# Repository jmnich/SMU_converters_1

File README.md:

# SMU_converters_1

ADC/DAC converters module for HTBlog Source Measure Unit

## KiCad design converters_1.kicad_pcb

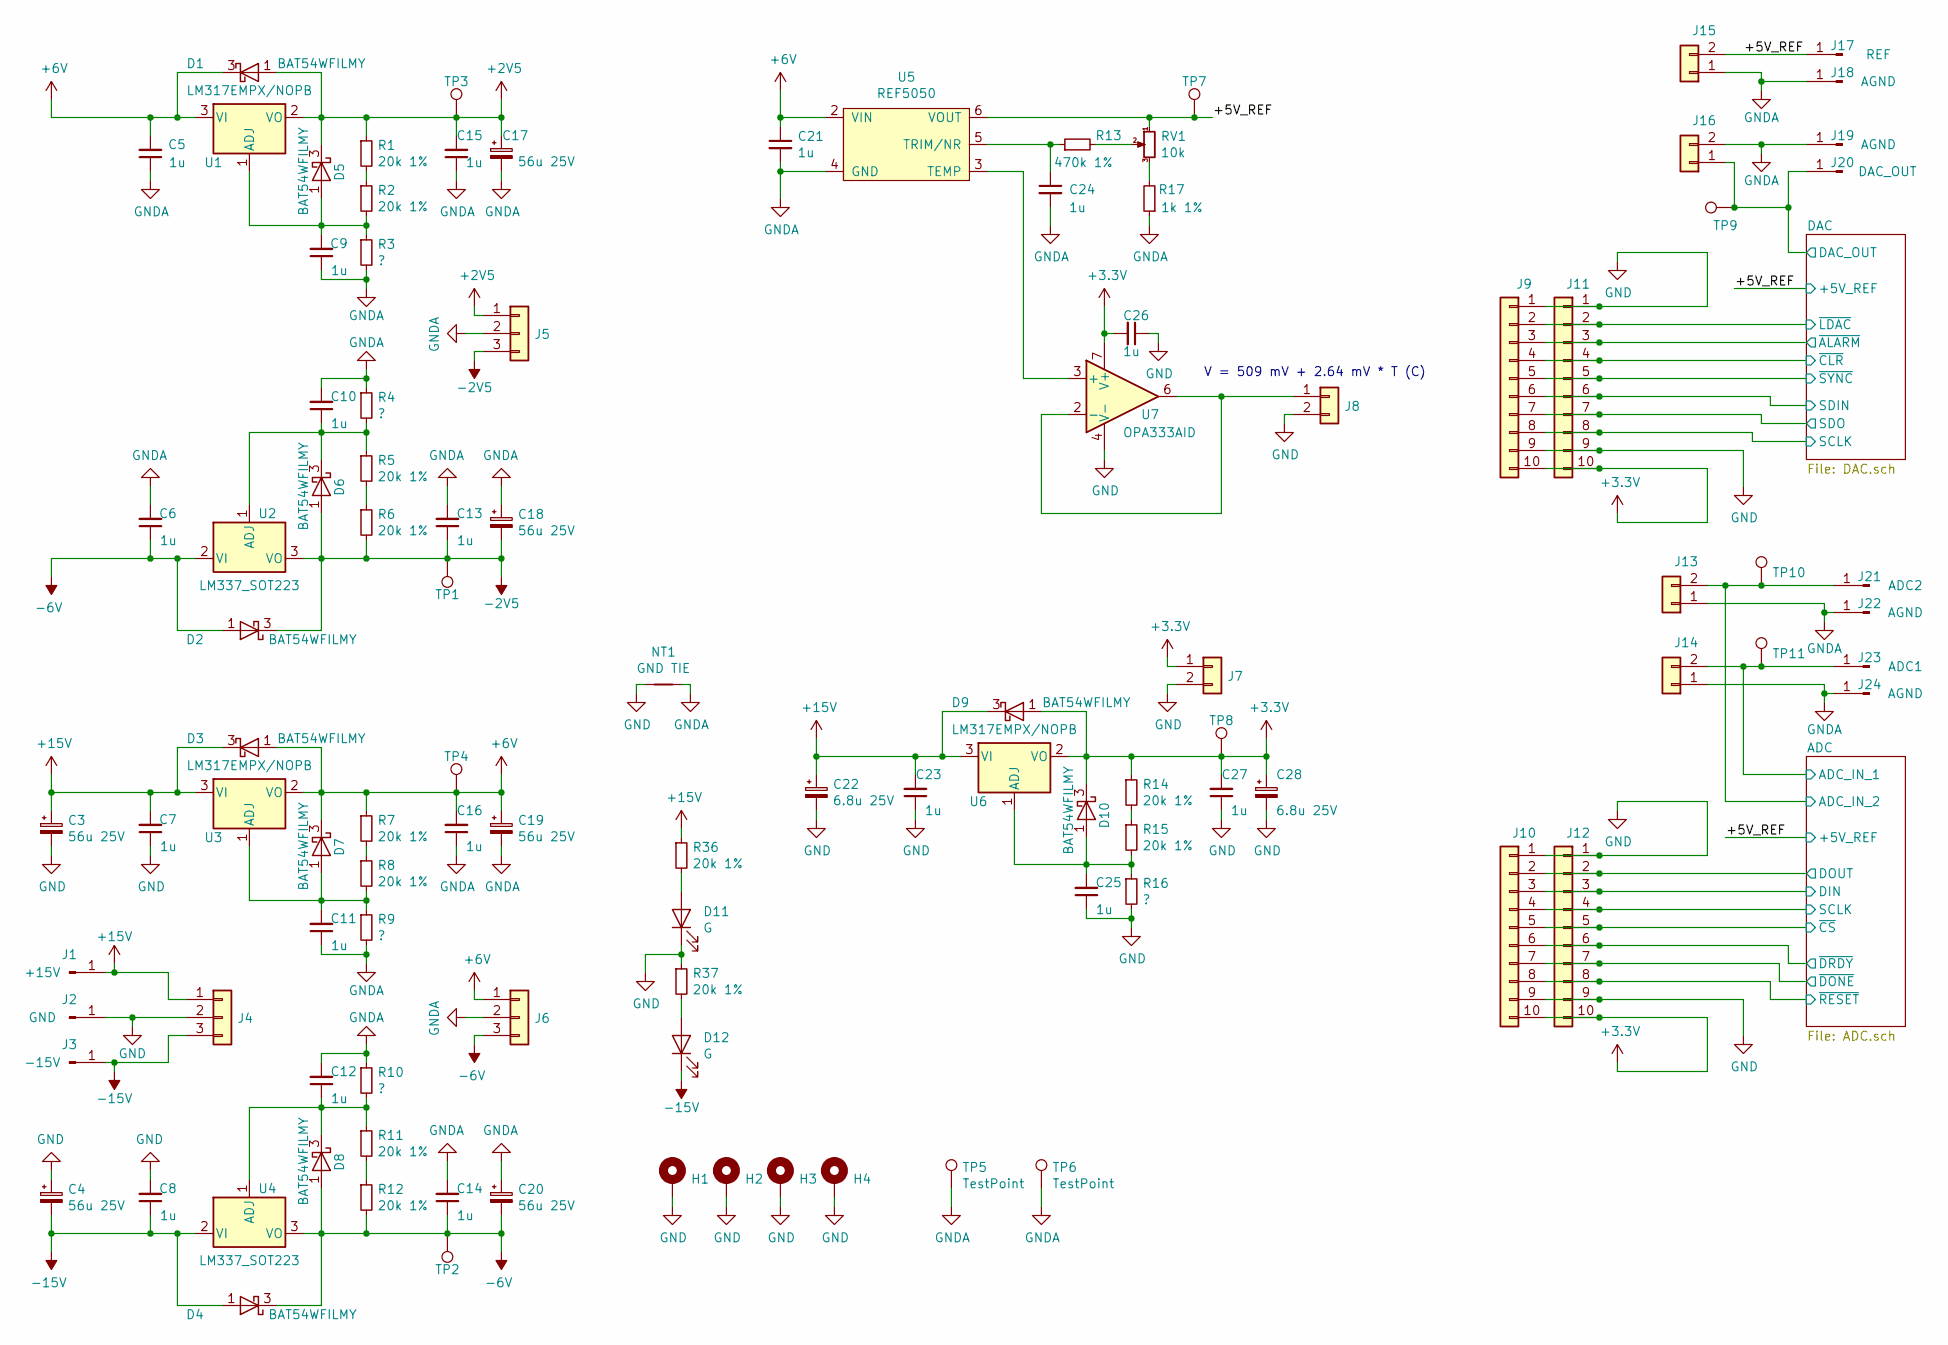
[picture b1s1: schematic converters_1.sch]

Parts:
C3, C4, C17, C18, C19, C20: 56u 25V; CP_Elec_6.3x5.9
C5, C6, C7, C8, C9, C10, C11, C12, C13, C14, C15, C16, C21, C23, C24, C25, C26, C27: 1u; C_0603_1608Metric_Pad1.05x0.95mm_HandSolder
C22, C28: 6.8u 25V; CP_Elec_6.3x5.9
D1, D2, D3, D4, D5, D6, D7, D8, D9, D10: BAT54WFILMY; SOT-323_SC-70
D11, D12: G; LED_0603_1608Metric_Pad1.05x0.95mm_HandSolder
H1, H2, H3, H4: MountingHole_Pad; MountingHole_3.2mm_M3_Pad_Via
J1: +15V; MountingHole_2.2mm_M2_Pad_Via
J2: GND; MountingHole_2.2mm_M2_Pad_Via
J3: -15V; MountingHole_2.2mm_M2_Pad_Via
J4, J5, J6: Conn_01x03; PinHeader_1x03_P2.54mm_Vertical
J7, J8, J13, J14, J15, J16: Conn_01x02; PinHeader_1x02_P2.54mm_Vertical
J9, J10, J11, J12: Conn_01x10; PinHeader_1x10_P2.54mm_Vertical
J17: REF; MountingHole_2.2mm_M2_Pad_Via
J18, J19, J22, J24: AGND; MountingHole_2.2mm_M2_Pad_Via
J20: DAC_OUT; MountingHole_2.2mm_M2_Pad_Via
J21: ADC2; MountingHole_2.2mm_M2_Pad_Via
J23: ADC1; MountingHole_2.2mm_M2_Pad_Via
NT1: GND TIE; NetTie-2_SMD_Pad2.0mm
R1, R2, R5, R6, R7, R8, R11, R12, R14, R15, R36, R37: 20k 1%; R_0603_1608Metric_Pad1.05x0.95mm_HandSolder
R3, R4, R9, R10, R16: ?; R_0603_1608Metric_Pad1.05x0.95mm_HandSolder
R13: 470k 1%; R_0603_1608Metric_Pad1.05x0.95mm_HandSolder
R17: 1k 1%; R_0603_1608Metric_Pad1.05x0.95mm_HandSolder
RV1: 10k; Potentiometer_Vishay_T73XW_Horizontal; MPN T73XW103KT20
TP1, TP2, TP3, TP4, TP5, TP6, TP7, TP8, TP9, TP10, TP11: TestPoint; TestPoint_Keystone_5010-5014_Multipurpose
U1, U3, U6: LM317EMPX/NOPB; SOT-223-3_TabPin2
U2, U4: LM337_SOT223; SOT-223-3_TabPin2
U5: REF5050; SOIC-8_3.9x4.9mm_P1.27mm
U7: OPA333AID; SOIC-8_3.9x4.9mm_P1.27mm

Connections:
+2V5: C15.2, C17.1, D1.1 (A), D5.3 (K), J5.1, R1.1, TP3.1, U1.2 (VO); also elsewhere on the board
+3V3: C26.2, C27.2, C28.1, D9.1 (A), D10.3 (K), J7.1, J9.10, J10.10, J11.10, J12.10, R14.1, TP8.1, U6.2 (VO), U7.7 (V+); also elsewhere on the board
+6V: C5.2, C16.2, C19.1, C21.1, D1.3 (K), D3.1 (A), D7.3 (K), J6.1, R7.1, TP4.1, U1.3 (VI), U3.2 (VO), U5.2 (VIN); also elsewhere on the board
+15V: C3.1, C7.2, C22.1, C23.2, D3.3 (K), D9.3 (K), J1.1, J4.1, R36.1, U3.3 (VI), U6.3 (VI)
-2V5: C13.1, C18.2, D2.3 (K), D6.1 (A), J5.3, R6.2, TP1.1, U2.3 (VO); also elsewhere on the board
-6V: C6.1, C14.1, C20.2, D2.1 (A), D4.3 (K), D8.1 (A), J6.3, R12.2, TP2.1, U2.2 (VI), U4.3 (VO); also elsewhere on the board
-15V: C4.2, C8.1, D4.1 (A), D12.1 (K), J3.1, J4.3, U4.2 (VI)
/+5V_REF: J15.2, J17.1, RV1.1, TP7.1, U5.6 (VOUT); also elsewhere on the board
/ADC/ADC_IN_1: J14.2, J23.1, TP11.1; also elsewhere on the board
/ADC/ADC_IN_2: J13.2, J21.1, TP10.1; also elsewhere on the board
/ADC/DIN: J10.3, J12.3; also elsewhere on the board
/ADC/DOUT: J10.2, J12.2; also elsewhere on the board
/ADC/SCLK: J10.4, J12.4; also elsewhere on the board
/ADC/~CS: J10.5, J12.5; also elsewhere on the board
/ADC/~DONE: J10.7, J12.7; also elsewhere on the board
/ADC/~DRDY: J10.6, J12.6; also elsewhere on the board
/ADC/~RESET: J10.8, J12.8; also elsewhere on the board
/DAC/DAC_OUT: J16.1, J20.1, TP9.1; also elsewhere on the board
/DAC/SCLK: J9.8, J11.8; also elsewhere on the board
/DAC/SDIN: J9.6, J11.6; also elsewhere on the board
/DAC/SDO: J9.7, J11.7; also elsewhere on the board
/DAC/~ALARM: J9.3, J11.3; also elsewhere on the board
/DAC/~CLR: J9.4, J11.4; also elsewhere on the board
/DAC/~LDAC: J9.2, J11.2; also elsewhere on the board
/DAC/~SYNC: J9.5, J11.5; also elsewhere on the board
unnamed: C9.2, D5.1 (A), R2.2, R3.1, U1.1 (ADJ)
unnamed: C10.1, D6.3 (K), R4.2, R5.1, U2.1 (ADJ)
unnamed: C11.2, D7.1 (A), R8.2, R9.1, U3.1 (ADJ)
unnamed: C12.1, D8.3 (K), R10.2, R11.1, U4.1 (ADJ)
unnamed: C24.1, R13.1, U5.5 (TRIM/NR)
unnamed: C25.2, D10.1 (A), R15.2, R16.1, U6.1 (ADJ)
unnamed: D11.2 (A), R36.2
unnamed: D12.2 (A), R37.2
unnamed: J8.1, U7.2 (-), U7.6
unnamed: R1.2, R2.1
unnamed: R5.2, R6.1
unnamed: R7.2, R8.1
unnamed: R11.2, R12.1
unnamed: R13.2, RV1.2
unnamed: R14.2, R15.1
unnamed: R17.2, RV1.3
unnamed: U5.3 (TEMP), U7.3 (+)

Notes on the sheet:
V = 509 mV + 2.64 mV * T (C)

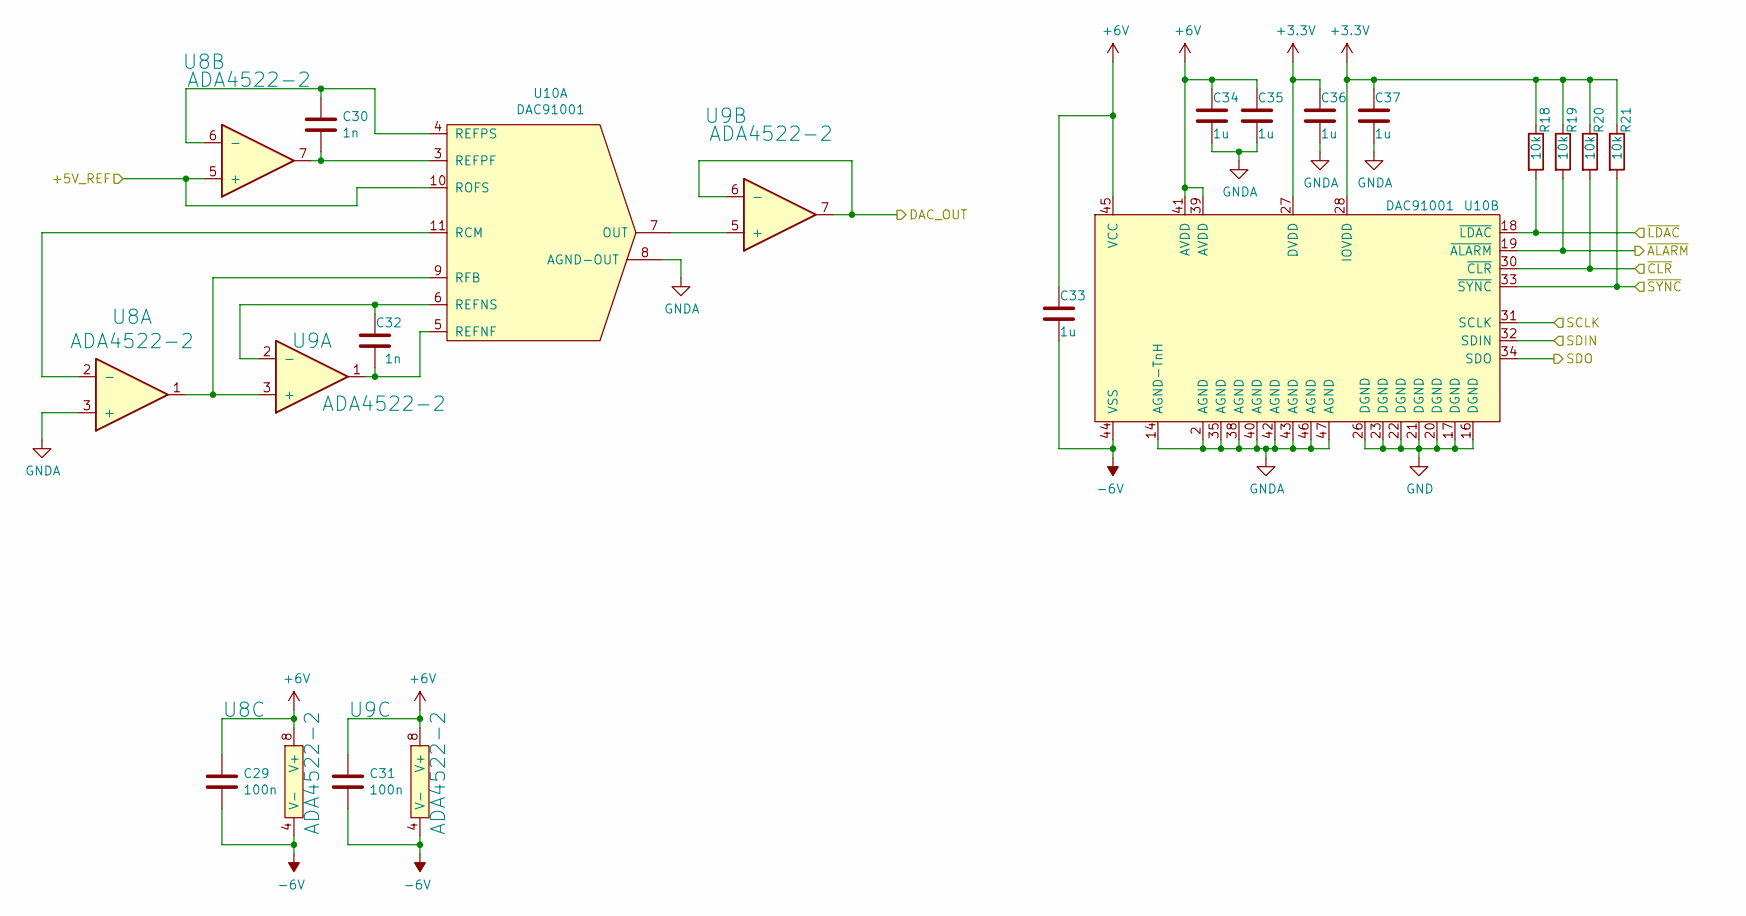
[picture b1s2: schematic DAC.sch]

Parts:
C29, C31: 100n; C_0603_1608Metric_Pad1.05x0.95mm_HandSolder
C30, C32: 1n; C_0603_1608Metric_Pad1.05x0.95mm_HandSolder
C33, C34, C35, C36, C37: 1u; C_0603_1608Metric_Pad1.05x0.95mm_HandSolder
R18, R19, R20, R21: 10k; R_0603_1608Metric_Pad1.05x0.95mm_HandSolder
U8, U9: ADA4522-2; MSOP-8_3x3mm_P0.65mm
U10: DAC91001; TQFP-48_7x7mm_P0.5mm

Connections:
+3V3: C36.1, C37.1, R18.1, R19.1, R20.1, R21.1, U10.27 (DVDD), U10.28 (IOVDD); also elsewhere on the board
+6V: C29.1, C31.1, C33.1, C34.1, C35.1, U8.8 (V+), U9.8 (V+), U10.39 (AVDD), U10.41 (AVDD), U10.45 (VCC); also elsewhere on the board
-6V: C29.2, C31.2, C33.2, U8.4 (V-), U9.4 (V-), U10.44 (VSS); also elsewhere on the board
/+5V_REF: U8.5 (+), U10.10 (ROFS); also elsewhere on the board
/DAC/DAC_OUT: U9.6 (-), U9.7; also elsewhere on the board
/DAC/SCLK: U10.31 (SCLK); also elsewhere on the board
/DAC/SDIN: U10.32 (SDIN); also elsewhere on the board
/DAC/SDO: U10.34 (SDO); also elsewhere on the board
/DAC/~ALARM: R19.2, U10.19 (~ALARM); also elsewhere on the board
/DAC/~CLR: R20.2, U10.30 (~CLR); also elsewhere on the board
/DAC/~LDAC: R18.2, U10.18 (~LDAC); also elsewhere on the board
/DAC/~SYNC: R21.2, U10.33 (~SYNC); also elsewhere on the board
unnamed: C30.1, U8.6 (-), U10.4 (REFPS)
unnamed: C30.2, U8.7, U10.3 (REFPF)
unnamed: C32.1, U9.2 (-), U10.6 (REFNS)
unnamed: C32.2, U9.1, U10.5 (REFNF)
unnamed: U9.5 (+), U10.7 (OUT)
unnamed: U8.1, U9.3 (+), U10.9 (RFB)
unnamed: U8.2 (-), U10.11 (RCM)

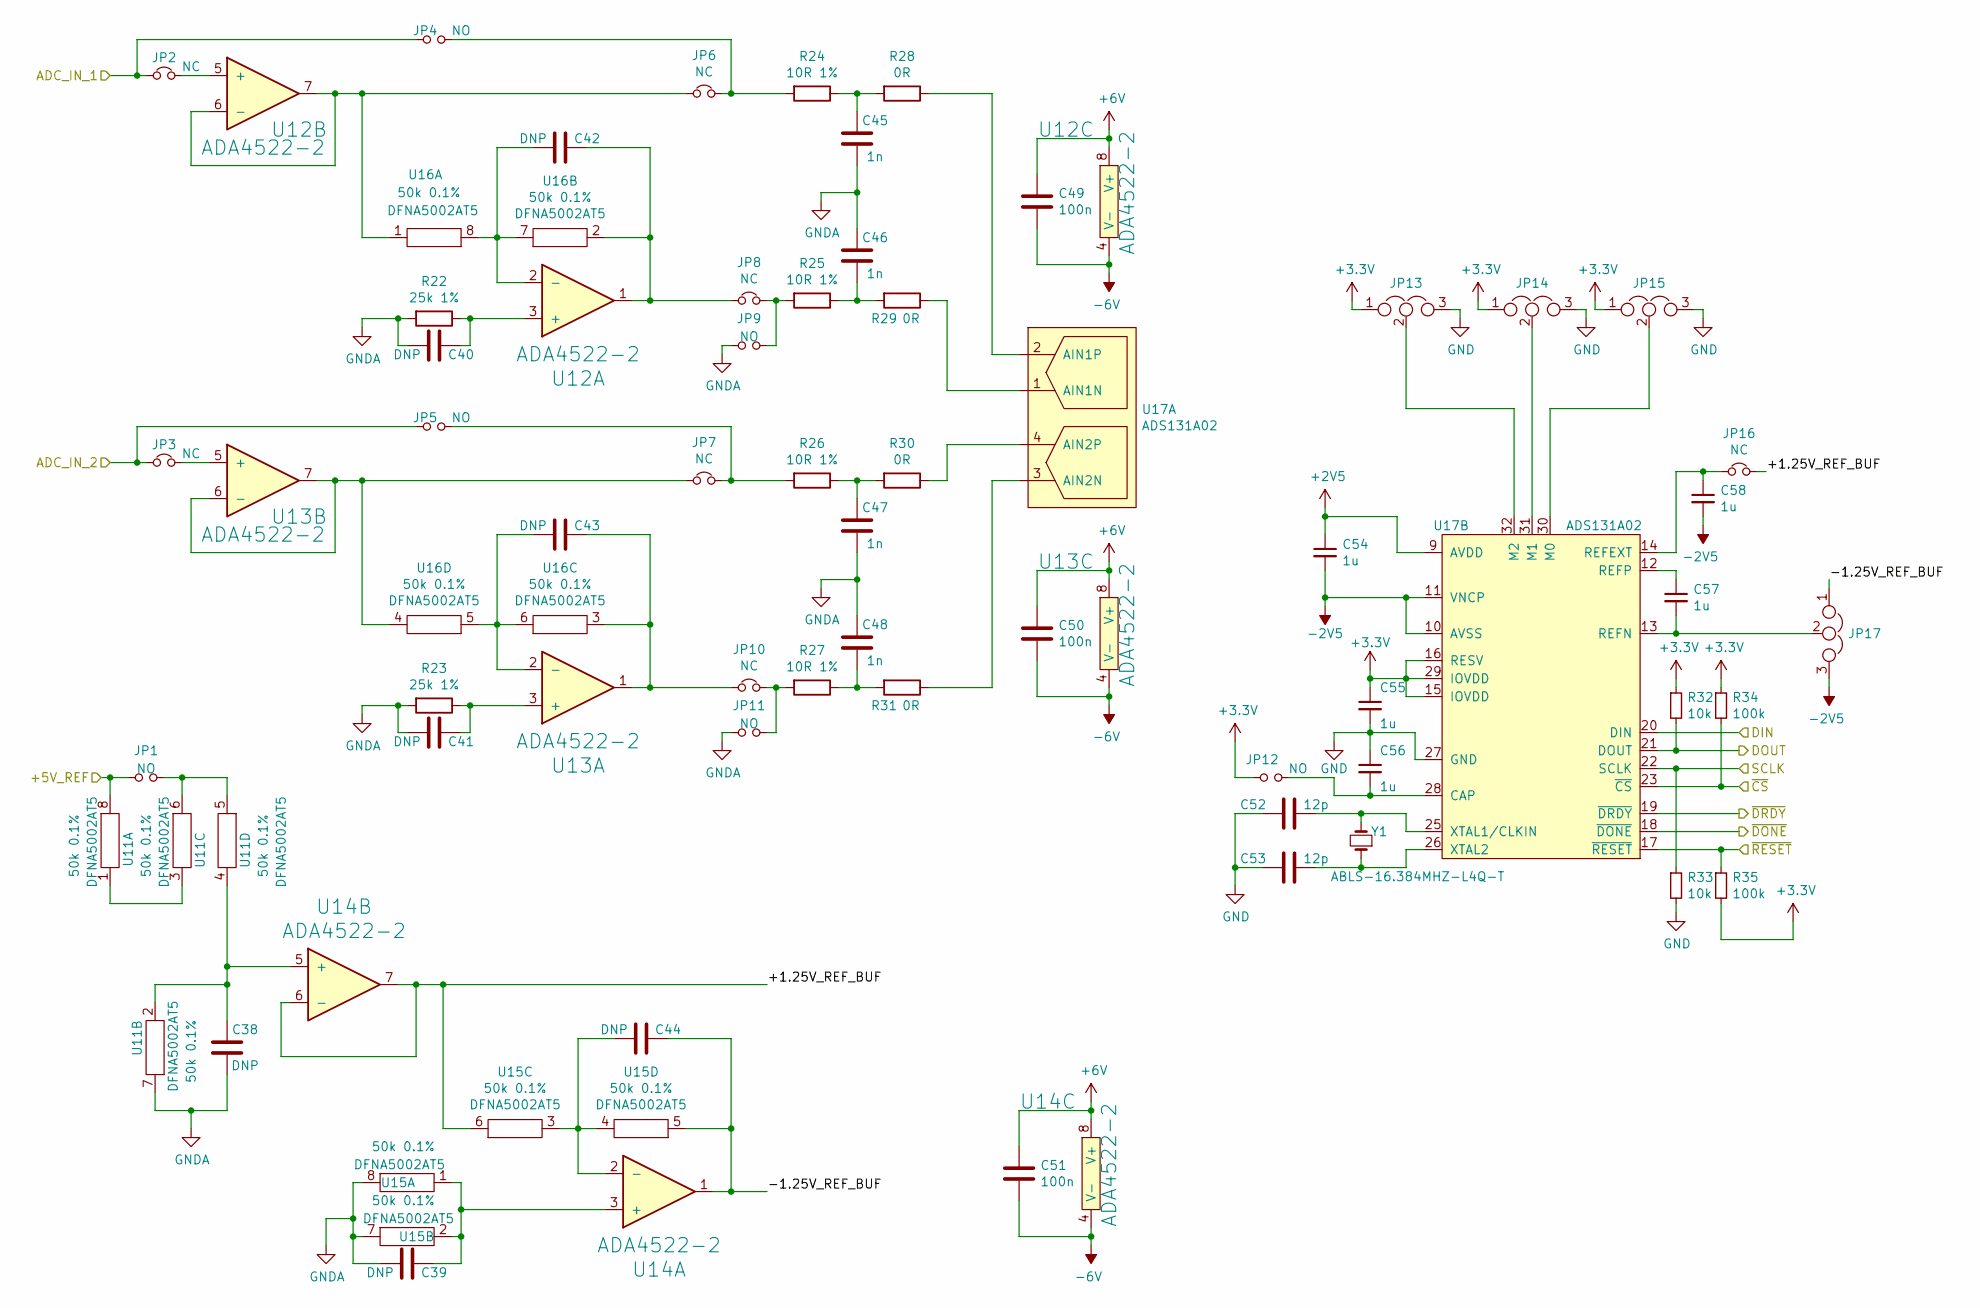
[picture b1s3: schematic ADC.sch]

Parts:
C38, C39, C40, C41, C42, C43, C44: DNP; C_0603_1608Metric_Pad1.05x0.95mm_HandSolder
C45, C46, C47, C48: 1n; C_0603_1608Metric_Pad1.05x0.95mm_HandSolder
C49, C50, C51: 100n; C_0603_1608Metric_Pad1.05x0.95mm_HandSolder
C52, C53: 12p; C_0603_1608Metric_Pad1.05x0.95mm_HandSolder
C54, C55, C56, C57, C58: 1u; C_0603_1608Metric_Pad1.05x0.95mm_HandSolder
JP1, JP4, JP5, JP9, JP11, JP12: NO; SolderJumper-2_P1.3mm_Open_RoundedPad1.0x1.5mm
JP2, JP3, JP6, JP7, JP8, JP10, JP16: NC; SolderJumper-2_P1.3mm_Open_RoundedPad1.0x1.5mm
JP13, JP14, JP15, JP17: Jumper_NC_Dual; SolderJumper-3_P1.3mm_Open_RoundedPad1.0x1.5mm
R22, R23: 25k 1%; R_0603_1608Metric_Pad1.05x0.95mm_HandSolder
R24, R25, R26, R27: 10R 1%; R_0603_1608Metric_Pad1.05x0.95mm_HandSolder
R28, R29, R30, R31: 0R; R_0603_1608Metric_Pad1.05x0.95mm_HandSolder
R32, R33: 10k; R_0603_1608Metric_Pad1.05x0.95mm_HandSolder
R34, R35: 100k; R_0603_1608Metric_Pad1.05x0.95mm_HandSolder
U11, U15, U16: 50k 0.1%; DFN-8-1EP_4x4mm_P0.8mm_EP2.3x3.24mm; MPN DFNA5002AT5
U12, U13, U14: ADA4522-2; MSOP-8_3x3mm_P0.65mm
U17: ADS131A02; LQFP-32_5x5mm_P0.5mm
Y1: ABLS-16.384MHZ-L4Q-T; Crystal_SMD_HC49-SD_HandSoldering

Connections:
+2V5: C54.1, U17.9 (AVDD); also elsewhere on the board
+3V3: C55.1, JP12.1, JP13.1, JP14.1, JP15.1, R32.1, R34.1, R35.2, U17.15 (IOVDD), U17.16 (RESV), U17.29 (IOVDD); also elsewhere on the board
+6V: C49.1, C50.1, C51.1, U12.8 (V+), U13.8 (V+), U14.8 (V+); also elsewhere on the board
-2V5: C54.2, C58.2, JP17.3, U17.10 (AVSS), U17.11 (VNCP); also elsewhere on the board
-6V: C49.2, C50.2, C51.2, U12.4 (V-), U13.4 (V-), U14.4 (V-); also elsewhere on the board
/+5V_REF: JP1.2, U11.8; also elsewhere on the board
/ADC/+1.25V_REF_BUF: JP16.2, U14.6 (-), U14.7, U15.6
/ADC/-1.25V_REF_BUF: C44.1, JP17.1, U14.1, U15.5
/ADC/ADC_IN_1: JP2.1, JP4.1; also elsewhere on the board
/ADC/ADC_IN_2: JP3.1, JP5.1; also elsewhere on the board
/ADC/DIN: U17.20 (DIN); also elsewhere on the board
/ADC/DOUT: R32.2, U17.21 (DOUT); also elsewhere on the board
/ADC/SCLK: R33.1, U17.22 (SCLK); also elsewhere on the board
/ADC/~CS: R34.2, U17.23 (~CS); also elsewhere on the board
/ADC/~DONE: U17.18 (~DONE); also elsewhere on the board
/ADC/~DRDY: U17.19 (~DRDY); also elsewhere on the board
/ADC/~RESET: R35.1, U17.17 (~RESET); also elsewhere on the board
unnamed: C38.2, U11.2, U11.4, U14.5 (+)
unnamed: C39.1, U14.3 (+), U15.1, U15.2
unnamed: C40.1, R22.1, U12.3 (+)
unnamed: C41.1, R23.1, U13.3 (+)
unnamed: C42.1, JP8.1, U12.1, U16.2
unnamed: C42.2, U12.2 (-), U16.7, U16.8
unnamed: C43.1, JP10.1, U13.1, U16.3
unnamed: C43.2, U13.2 (-), U16.5, U16.6
unnamed: C44.2, U14.2 (-), U15.3, U15.4
unnamed: C45.2, R24.1, R28.2
unnamed: C46.1, R25.1, R29.2
unnamed: C47.2, R26.1, R30.2
unnamed: C48.1, R27.1, R31.2
unnamed: C52.2, U17.25 (XTAL1/CLKIN), Y1.2
unnamed: C53.2, U17.26 (XTAL2), Y1.1
unnamed: C56.2, JP12.2, U17.28 (CAP)
unnamed: C57.1, U17.12 (REFP)
unnamed: C57.2, JP17.2, U17.13 (REFN)
unnamed: C58.1, JP16.1, U17.14 (REFEXT)
unnamed: JP1.1, U11.5, U11.6
unnamed: JP2.2, U12.5 (+)
unnamed: JP3.2, U13.5 (+)
unnamed: JP4.2, JP6.2, R24.2
unnamed: JP5.2, JP7.2, R26.2
unnamed: JP6.1, U12.6 (-), U12.7, U16.1
unnamed: JP7.1, U13.6 (-), U13.7, U16.4
unnamed: JP8.2, JP9.1, R25.2
unnamed: JP10.2, JP11.1, R27.2
unnamed: JP13.2, U17.32 (M2)
unnamed: JP14.2, U17.31 (M1)
unnamed: JP15.2, U17.30 (M0)
unnamed: R28.1, U17.2 (AIN1P)
unnamed: R29.1, U17.1 (AIN1N)
unnamed: R30.1, U17.4 (AIN2P)
unnamed: R31.1, U17.3 (AIN2N)
unnamed: U11.1, U11.3

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
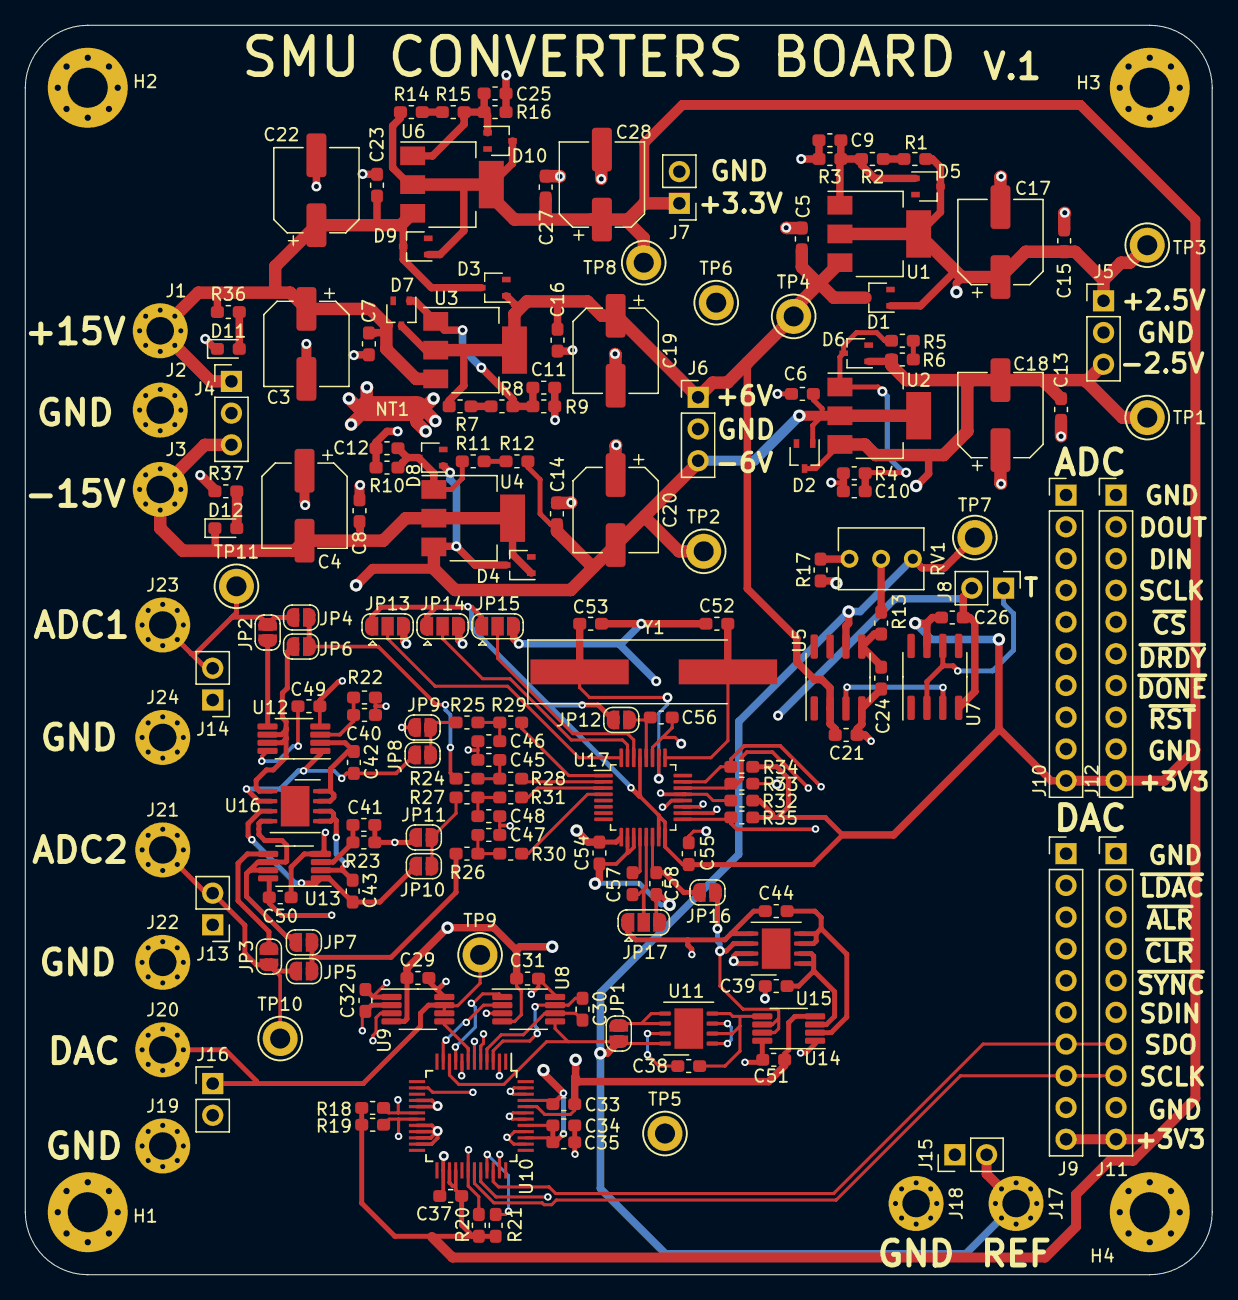
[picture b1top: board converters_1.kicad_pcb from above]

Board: 4 copper layers, 95.0 x 100.0 mm, 180 parts (0 on the bottom side), 89 nets.

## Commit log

2020-10-17 sch in progress
2020-10-18 schematics done
2020-10-27 board routed
    ready for production
2020-10-27 manufacturing files created
2020-10-27 3d image
2020-10-27 readme fix
2020-10-28 GND - AGND tie added
